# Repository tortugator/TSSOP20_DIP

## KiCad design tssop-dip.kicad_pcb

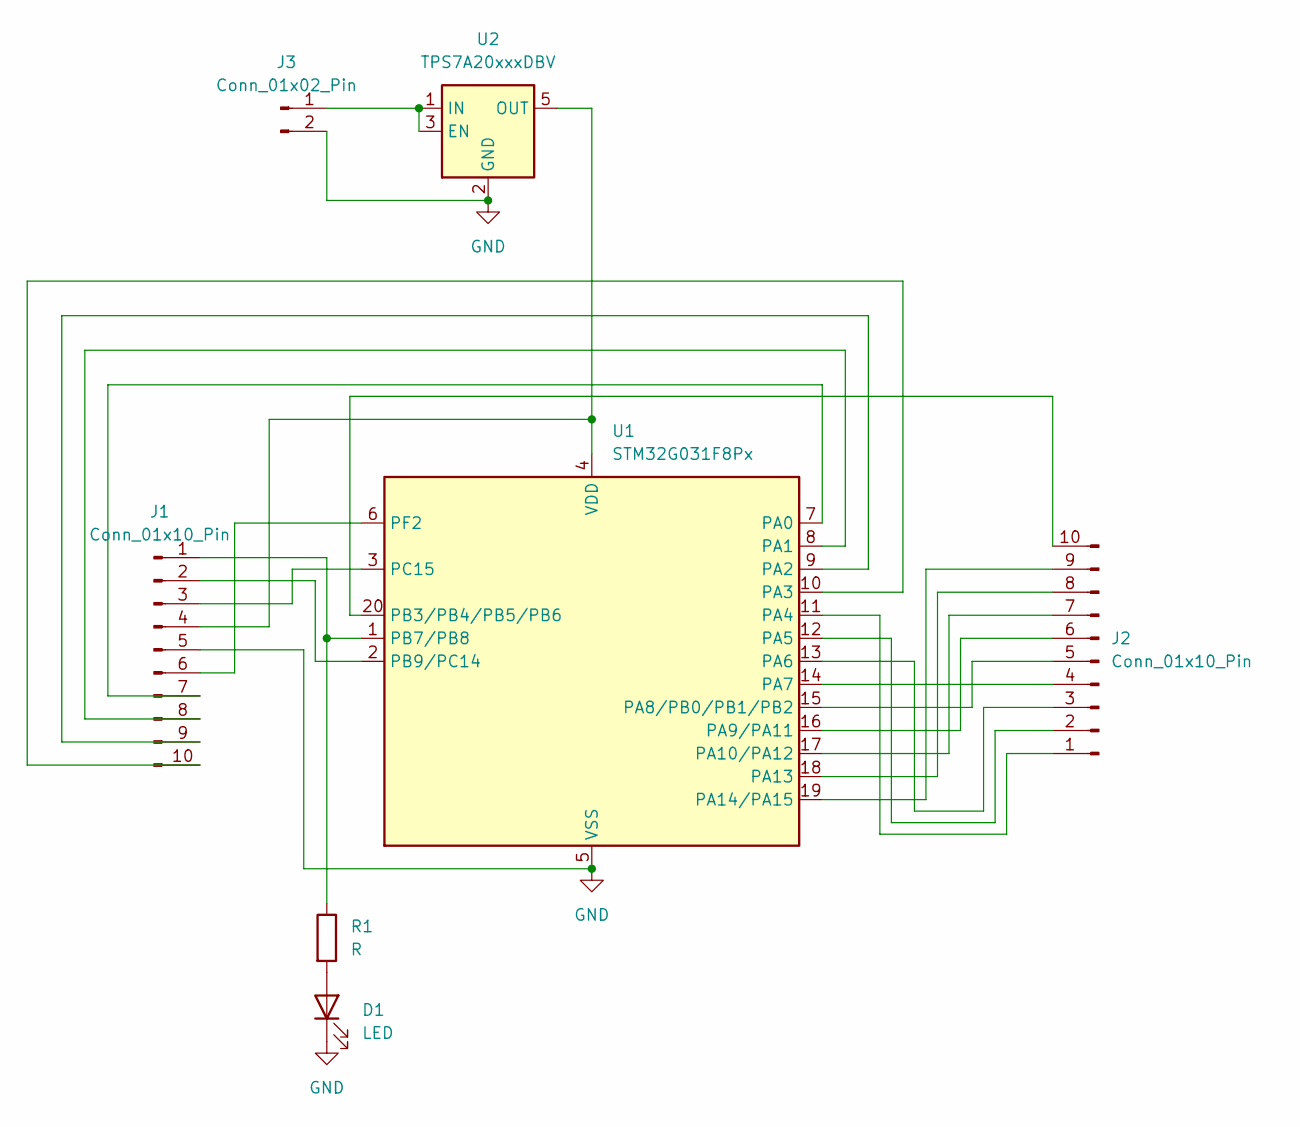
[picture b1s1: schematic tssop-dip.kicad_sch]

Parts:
D1: LED; LED_1206_3216Metric
J1, J2: Conn_01x10_Pin; PinHeader_1x10_P2.54mm_Vertical
J3: Conn_01x02_Pin; PinHeader_1x02_P2.54mm_Horizontal
R1: R; R_0805_2012Metric
U1: STM32G031F8Px; TSSOP-20_4.4x6.5mm_P0.65mm
U2: TPS7A20xxxDBV; SOT-23-5

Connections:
GND: D1.1 (K), J1.5, J3.2, U1.5 (VSS), U2.2 (GND)
unnamed: D1.2 (A), R1.2
unnamed: J1.1, R1.1, U1.1 (PB7/PB8)
unnamed: J1.2, U1.2 (PB9/PC14)
unnamed: J1.3, U1.3 (PC15)
unnamed: J1.4, U1.4 (VDD), U2.5 (OUT)
unnamed: J1.6, U1.6 (PF2)
unnamed: J1.7, U1.7 (PA0)
unnamed: J1.8, U1.8 (PA1)
unnamed: J1.9, U1.9 (PA2)
unnamed: J1.10, U1.10 (PA3)
unnamed: J2.1, U1.11 (PA4)
unnamed: J2.2, U1.12 (PA5)
unnamed: J2.3, U1.13 (PA6)
unnamed: J2.4, U1.14 (PA7)
unnamed: J2.5, U1.15 (PA8/PB0/PB1/PB2)
unnamed: J2.6, U1.16 (PA9/PA11)
unnamed: J2.7, U1.17 (PA10/PA12)
unnamed: J2.8, U1.18 (PA13)
unnamed: J2.9, U1.19 (PA14/PA15)
unnamed: J2.10, U1.20 (PB3/PB4/PB5/PB6)
unnamed: J3.1, U2.1 (IN), U2.3 (EN)

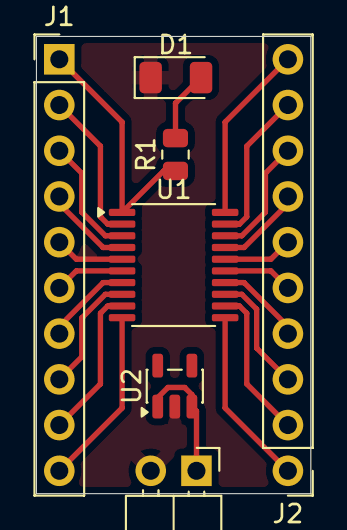
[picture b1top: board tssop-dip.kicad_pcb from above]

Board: 2 copper layers, 15.2 x 25.4 mm, 7 parts (0 on the bottom side), 22 nets.
